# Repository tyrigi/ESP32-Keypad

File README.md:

# ESP32-Keypad

Update: I've started a [Hackaday.io project](https://hackaday.io/project/177226-esp32-bluetooth-gamepad)!

This is a modification to the [Sherbet gaming keypad](https://www.billiam.org/2019/05/29/sherbet-an-ergonomic-keypad) designed by [Billiam](https://www.billiam.org/). The intent is to turn it into a battery-powered bluetooth peripheral. I'm using the ESP32 Arduino libraries, but I'm working in VSCode with [esp-idf](https://github.com/espressif/esp-idf) and [PlatformIO](https://platformio.org/install/ide?install=vscode).

The main reason for not working in the Arduino IDE is the library screwy-ness that is required here. The Sherbet gamepad has an analog stick in addition to regular keyboard inputs, which requires the use of Keyboard HID and Gamepad HID. Both of these options are widely available and pretty easy to implement, but I've been unsuccessful in finding a solution that implements both. Due to how the ESP32-Arduino libraries for both of these options work, the libraries need to be combined into one freakish combination. 

The library I'm using is a combination of the following two libraries:

[ESP32-BLE-Keyboard](https://github.com/T-vK/ESP32-BLE-Keyboard) written by [T-vK](https://github.com/T-vK)

[ESP32-BLE-Gamepad](https://github.com/lemmingDev/ESP32-BLE-Gamepad) written by [lemmingDev](https://github.com/lemmingDev)

I've created a breakout board with an ESP32-WROOM-32E chip that has support for a Li-Ion battery. The Eagle design files, datasheets for critical parts, and a DigiKey BOM have been included for anyone wanting to make one of these for themselves!

Notes:

There have been some issues with my board files. As a disclaimer, older versions of the PCB have pin 32 connected directly to Battery +. I wanted to use the ADC on pin 32 to measure battery voltage, and from there remaining battery capacity. I forgot however that a fully charged Li-Ion battery is 4.2V, which exceeds the ESP32's max input voltage by 0.5V. Not enough to fry the chip, but more than enough to damage the pin. The end effect is that this blasts the UART RX channel in the chip with 4V, rendering the ESP unable to receive new code over the UART interface. So if you're using an old board version, make sure to cut the trace going to I/O pin 32. You've been warned. 

I've since changed this to be fed through a voltage divider to measure the battery. It's constantly draining the battery, but the divider only draws about 9 micro amps, so it shouldn't impact lifespan.

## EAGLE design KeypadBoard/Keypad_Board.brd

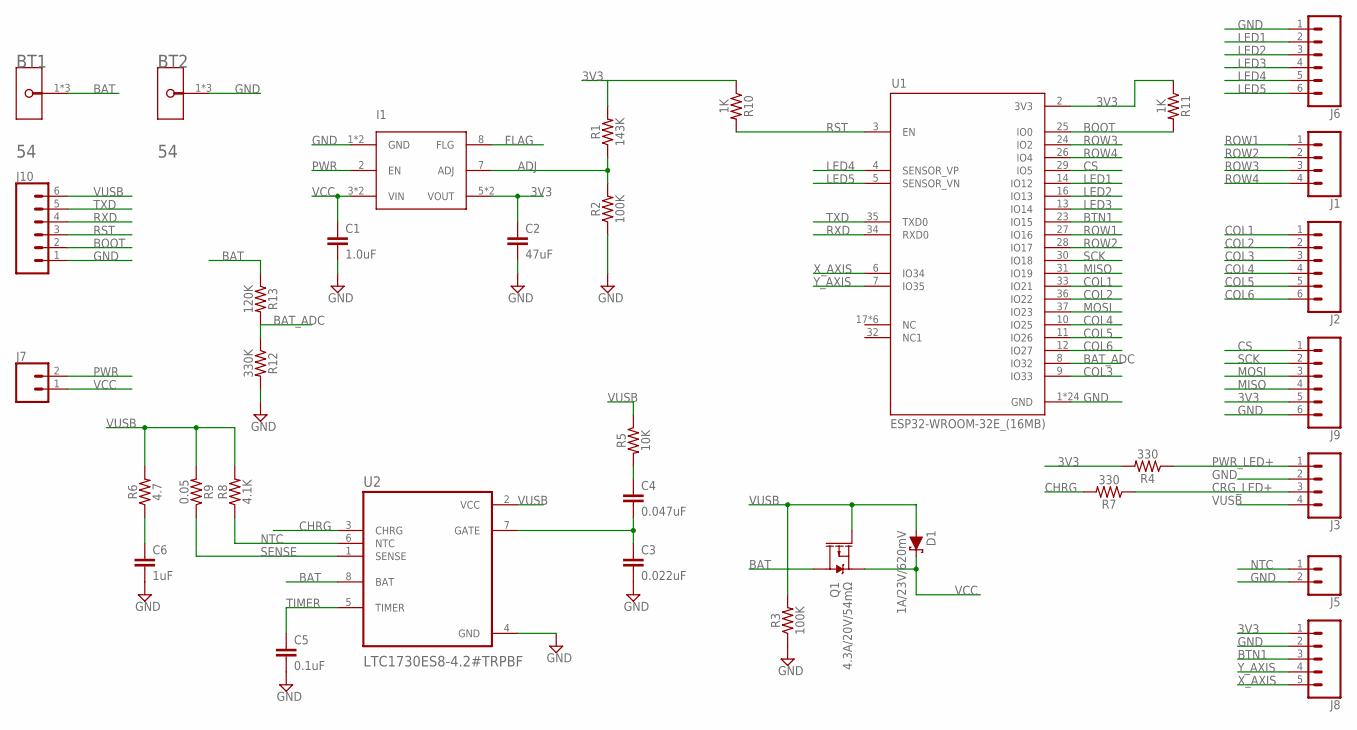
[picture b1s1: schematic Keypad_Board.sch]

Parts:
BT1, BT2: KEYSTONE_54KEYSTONE_54_0_0; KEYSTONE_54_0
C1: 1.0uF; 1206
C2: 47uF; 1206
C3: 0.022uF; 0603
C4: 0.047uF; 0603
C5: 0.1uF; 0603
C6: 1uF; 0603
D1: 1A/23V/620mV; SOD-323
I1: MIC37303; SOIC8
J1, J3: CONN_04; 1X04
J2, J6, J9, J10: CONN_06LOCK; 1X06_LOCK
J5, J7: CONN_02; 1X02
J8: CONN_05; 1X05
Q1: 4.3A/20V/54mΩ; SOT23-3
R1: 143K; 1206
R2, R3: 100K; 1206
R4, R7: 330; 0805
R5: 10K; 0805
R6: 4.7; 0603
R8: 4.1K; 0603
R9: 0.05; 0603
R10, R11: 1K; 0805
R12: 330K; 0805
R13: 120K; 0805
U1: ESP32-WROOM-32E_(16MB); MODULE_ESP32-WROOM-32E_(16MB)
U2: LTC1730ES8-4.2#TRPBF; SO-8_S

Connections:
3V3: C2.1, I1.5 (VOUT), I1.6 (VOUT), J8.1, J9.5, R1.2, R4.2, R10.1, R11.1, U1.2 (3V3)
ADJ: I1.7 (ADJ), R1.1, R2.2
BAT: BT1.1, BT1.1-2, BT1.1-3, Q1.3 (D), R13.1, U2.8 (BAT)
BAT_ADC: R12.1, R13.2, U1.8 (IO32)
BOOT: J10.2, R11.2, U1.25 (IO0)
BTN1: J8.3, U1.23 (IO15)
CHRG: R7.2, U2.3 (CHRG)
COL1: J2.1, U1.33 (IO21)
COL2: J2.2, U1.36 (IO22)
COL3: J2.3, U1.9 (IO33)
COL4: J2.4, U1.10 (IO25)
COL5: J2.5, U1.11 (IO26)
COL6: J2.6, U1.12 (IO27)
CRG_LED+: J3.3, R7.1
CS: J9.1, U1.29 (IO5)
FLAG: I1.8 (FLG)
GND: BT2.1, BT2.1-2, BT2.1-3, C1.2, C2.2, C3.2, C5.2, C6.2, I1.1 (GND), I1.9 (GND), J3.2, J5.2, J6.1, J8.2, J9.6, J10.1, R2.1, R3.1, R12.2, U1.1 (GND), U1.15 (GND), U1.38 (GND), U1.39_1 (GND), U1.39_2 (GND), U1.39_3 (GND), U1.39_4 (GND), U1.39_5 (GND), U1.39_6 (GND), U1.39_7 (GND), U1.39_8 (GND), U1.39_9 (GND), U1.39_10 (GND), U1.39_11 (GND), U1.39_12 (GND), U1.39_13 (GND), U1.39_14 (GND), U1.39_15 (GND), U1.39_16 (GND), U1.39_17 (GND), U1.39_18 (GND), U1.39_19 (GND), U1.39_20 (GND), U1.39_21 (GND), U2.4 (GND)
LED1: J6.2, U1.14 (IO12)
LED2: J6.3, U1.16 (IO13)
LED3: J6.4, U1.13 (IO14)
LED4: J6.5, U1.4 (SENSOR_VP)
LED5: J6.6, U1.5 (SENSOR_VN)
MISO: J9.4, U1.31 (IO19)
MOSI: J9.3, U1.37 (IO23)
unnamed: C4.1, R5.2
unnamed: C3.1, C4.2, U2.7 (GATE)
unnamed: C6.1, R6.1
NTC: J5.1, R8.1, U2.6 (NTC)
PWR: I1.2 (EN), J7.2
PWR_LED+: J3.1, R4.1
ROW1: J1.1, U1.27 (IO16)
ROW2: J1.2, U1.28 (IO17)
ROW3: J1.3, U1.24 (IO2)
ROW4: J1.4, U1.26 (IO4)
RST: J10.3, R10.2, U1.3 (EN)
RXD: J10.4, U1.34 (RXD0)
SCK: J9.2, U1.30 (IO18)
SENSE: R9.1, U2.1 (SENSE)
TIMER: C5.1, U2.5 (TIMER)
TXD: J10.5, U1.35 (TXD0)
VCC: C1.1, D1.C, I1.3 (VIN), I1.4 (VIN), J7.1, Q1.2 (S)
VUSB: D1.A, J3.4, J10.6, Q1.1 (G), R3.2, R5.1, R6.2, R8.2, R9.2, U2.2 (VCC)
X_AXIS: J8.5, U1.6 (IO34)
Y_AXIS: J8.4, U1.7 (IO35)

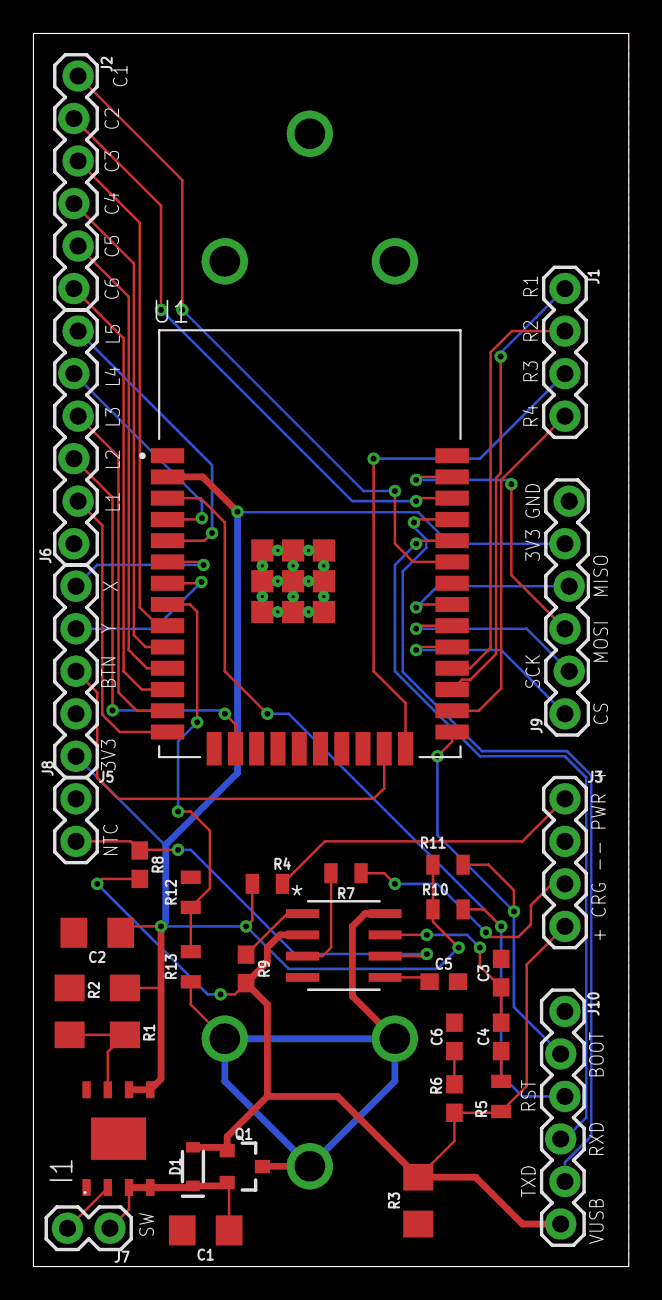
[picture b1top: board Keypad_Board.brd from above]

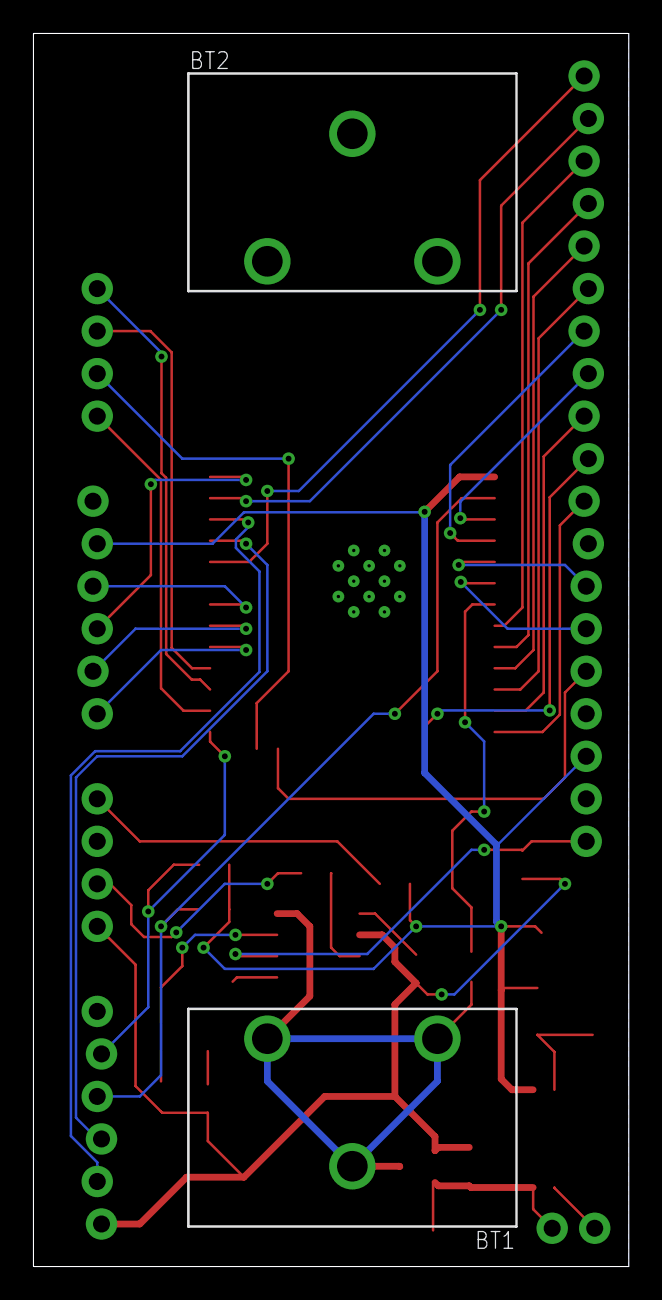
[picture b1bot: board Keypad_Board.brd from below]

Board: 2 copper layers, 35.6 x 73.7 mm, 35 parts (2 on the bottom side), 43 nets.

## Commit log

2021-01-14 Adding existing work
2021-01-14 Including forked library in main project since it's all one thing
2021-01-14 First successful build
2021-01-14 Working pushbutton inputs triggering keypresses
2021-01-15 Adding board design progress and datasheets for critical components
2021-01-15 First draft of board layout
2021-01-16 Completed board layout, Rev 1
2021-01-16 Added DigiKey BOM that can be imported into DigiKey
2021-01-16 Added description and links for other information
2021-01-18 Keyboard HID over bluetooth functional
2021-01-18 Initial XInput implementation attempt
2021-01-18 Switched from XInput to HID Gamepad, integration builds but doesn't work yet
2021-01-18 Working HIDReportDescriptor - Recognized as a gamepad and emits keypresses
2021-01-18 All but joystick working
2021-01-20 Board Rev2
2021-01-21 Analog stick working
2021-01-26 Board updates - ADC OverVoltage fix
2021-01-29 Joystick constantly re-calibrates to avoid weird drift
2021-01-29 Update README.md
    Added board defect warning
2021-01-30 Added battery level monitoring and charge LED
2021-01-30 Updated board for connection of a Micro SD Card module
2021-01-31 Removed debugging lines, added comments, and reduced power draw
2021-01-31 Board V4 - integrated battery holder, SD Breakout, mode LED's
2021-01-31 Removed junk files
2021-02-01 Added link to Hackaday.io project
2021-02-11 Updated schematic pdf
2021-02-19 Fixed issue where keypresses would still emit a notify
2021-03-15 Cleaned up code and added comments
2022-01-08 Code in working state, no user config

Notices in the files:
parts and their libraries:
SparkFun-Capacitors: Licensing: Creative Commons ShareAlike 4.0 International - https://creativecommons.org/licenses/by-sa/4.0
